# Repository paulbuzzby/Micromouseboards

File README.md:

# Micromouseboards
Here are different sets of PCBs for various Micro Mouse applications. This is the start of me using KiCad. I make no promises that any of this works.

Some of these boards (MouseSMDUKMARSAdvancedBoard and MouseMainboardTemplate) started as UKMARS boards that can be found [Here](https://github.com/ukmars/ukmarsbot)

All credit to Peter Harrison for the original design of these boards

Circuit design for the other boards is credited to Duncan Louttit

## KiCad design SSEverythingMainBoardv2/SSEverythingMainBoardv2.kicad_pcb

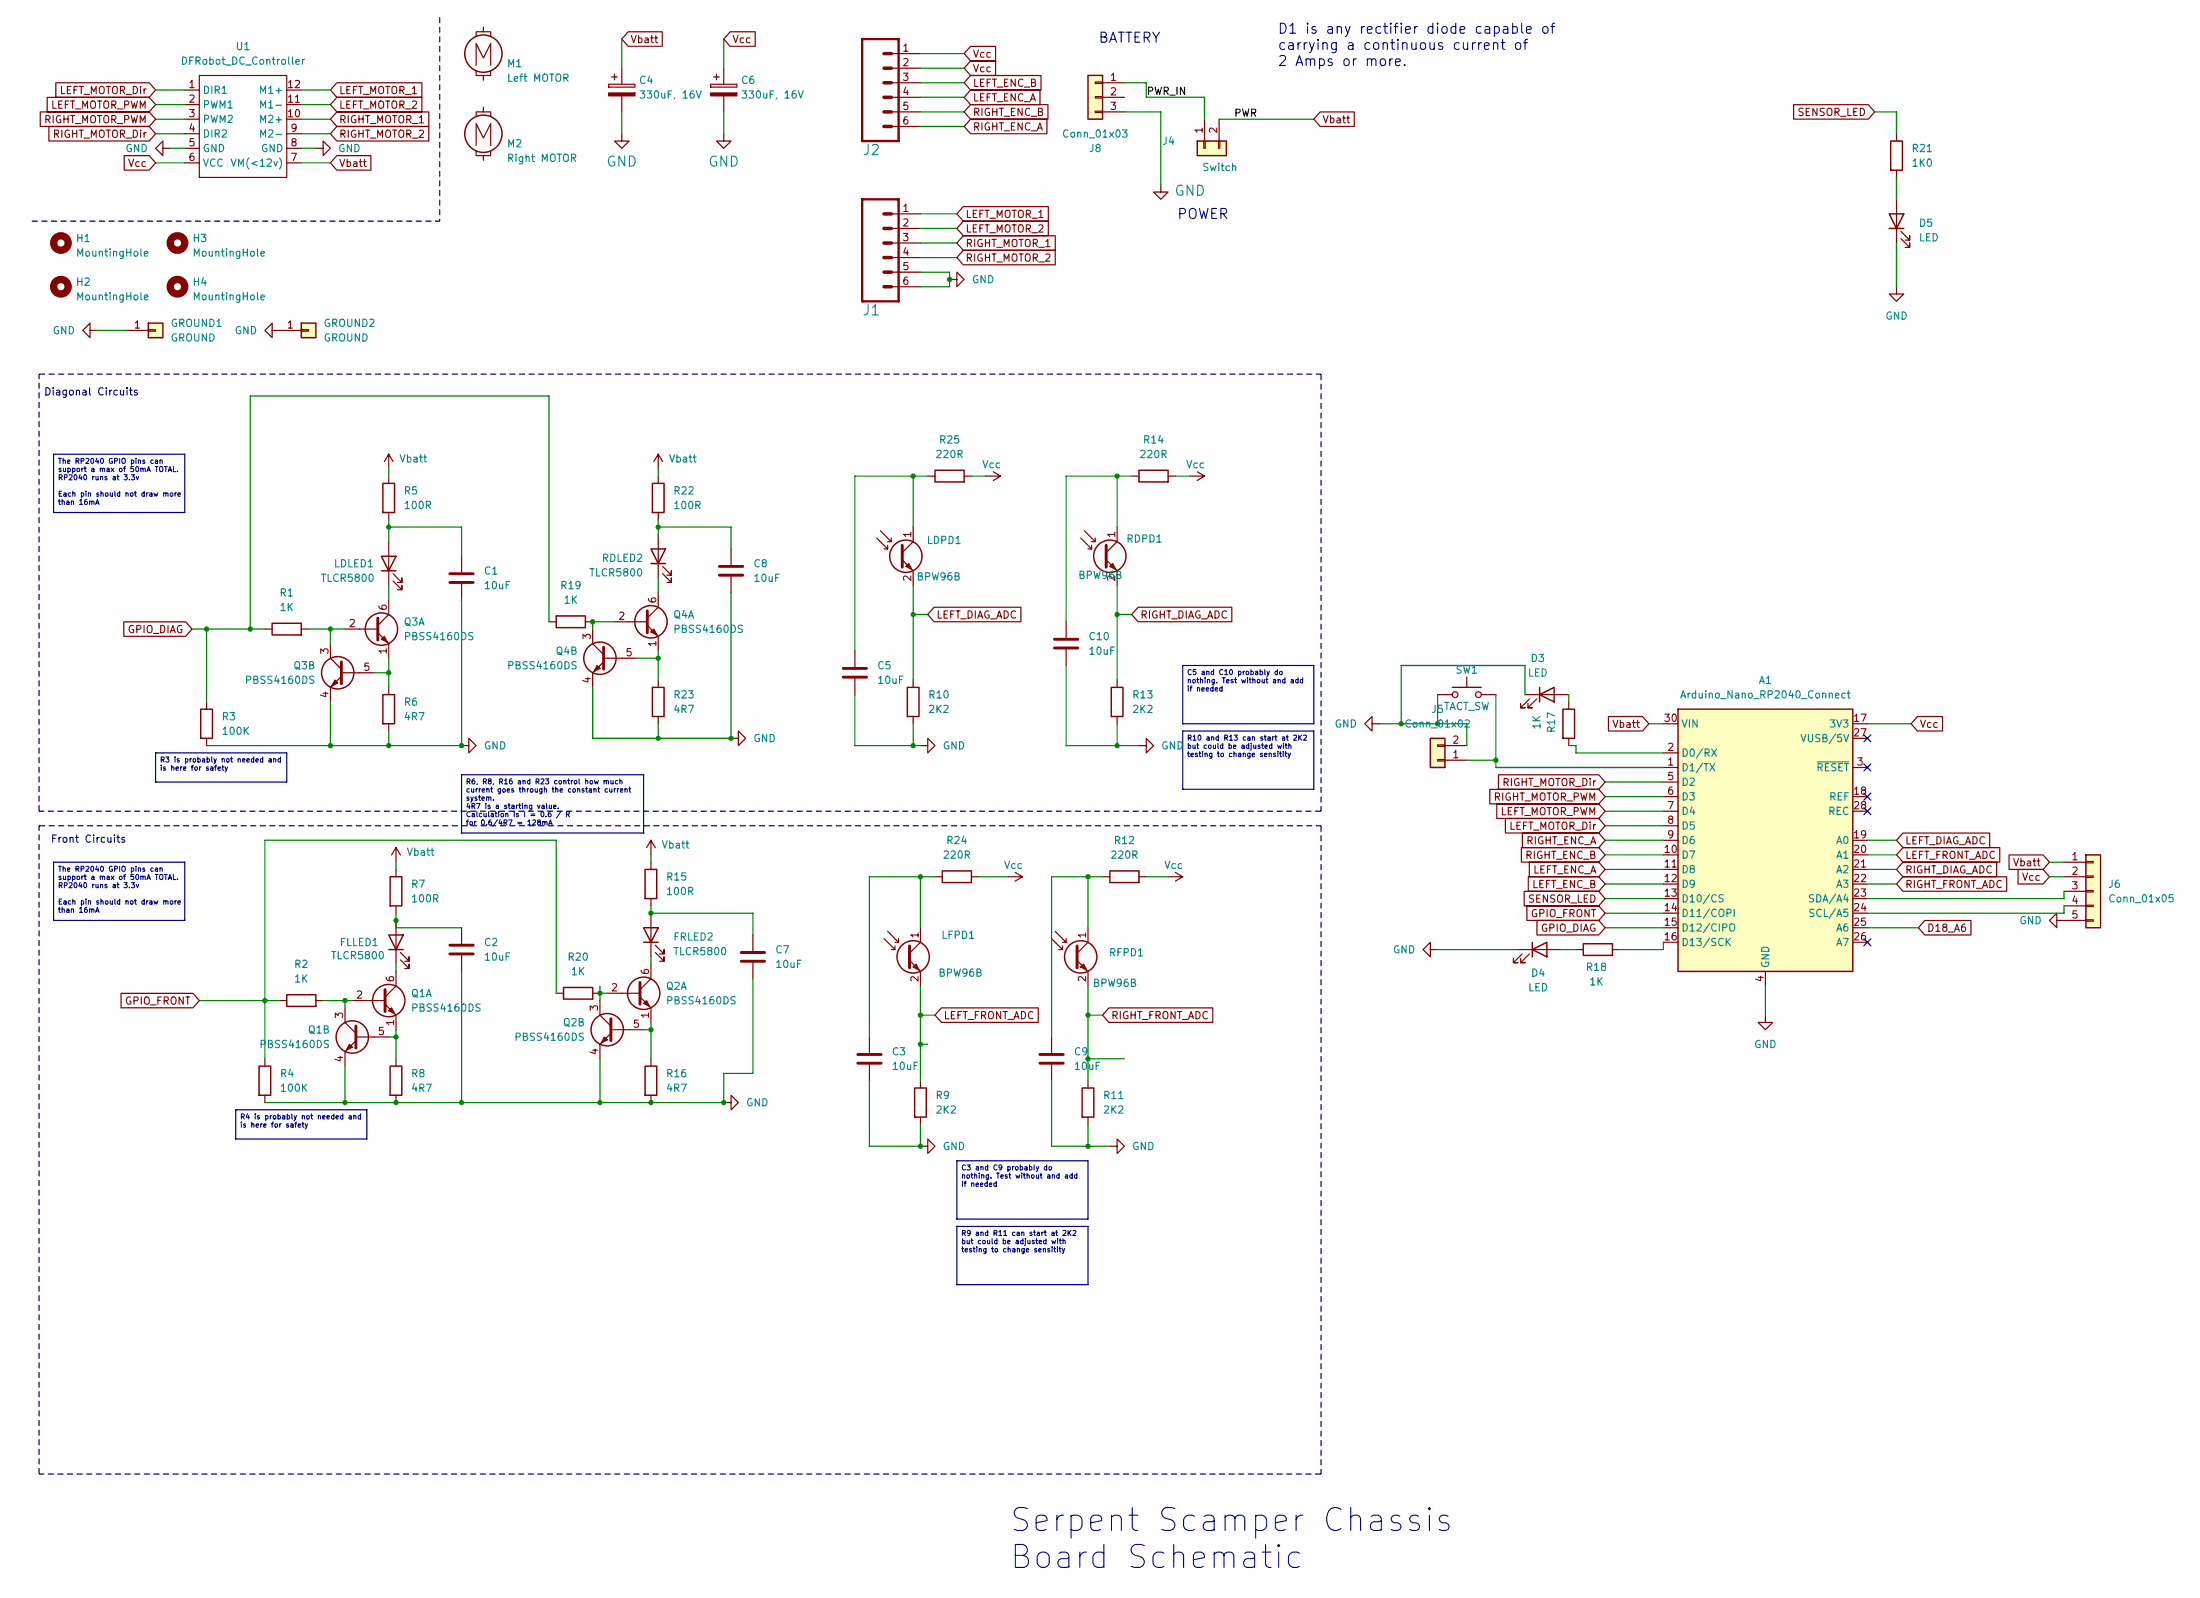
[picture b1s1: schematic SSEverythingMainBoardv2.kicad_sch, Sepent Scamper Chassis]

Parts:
A1: Arduino_Nano_RP2040_Connect; Arduino_Nano
C1, C2, C3, C5, C7, C8, C9, C10: 10uF; C_1206_3216Metric_Pad1.33x1.80mm_HandSolder
C4, C6: 330uF, 16V; C_Radial_D6.3mm_H7.0mm_P2.50mm
D3, D4, D5: LED; LED_1206_3216Metric_Pad1.42x1.75mm_HandSolder
FLLED1: TLCR5800; LED_D5.0mm_Horizontal_O1.27mm_Z3.0mm
FRLED2: TLCR5800; LED_D5.0mm_Horizontal_O1.27mm_Z3.0mm
GROUND1, GROUND2: GROUND; PinHeader_1x01_P2.54mm_Vertical
H1, H2, H3, H4: MountingHole; MountingHole_3.2mm_M3_clearance
J1, J2: CONN_06SILK_FEMALE_PTH; 1X06_LOCK_LONGPADS
J4: Switch; PinHeader_1x02_P2.54mm_Vertical
J5: Conn_01x02; PinHeader_1x02_P2.54mm_Vertical
J6: Conn_01x05; PinSocket_1x05_P2.54mm_Vertical
J8: Conn_01x03; JST_XH_B3B-XH-A_1x03_P2.50mm_Vertical
LDLED1: TLCR5800; LED_D5.0mm_Horizontal_O1.27mm_Z3.0mm
LDPD1: BPW96B; LED_D5.0mm_Horizontal_O1.27mm_Z3.0mm
LFPD1: BPW96B; LED_D5.0mm_Horizontal_O1.27mm_Z3.0mm
M1: Left MOTOR; MINI-METAL-GEARMOTOR-WITH-BRACKET
M2: Right MOTOR; MINI-METAL-GEARMOTOR-WITH-BRACKET_Alt
Q1, Q2, Q3, Q4: PBSS4160DS; SOT95P275X110-6N
R1, R2, R17, R18, R19, R20: 1K; R_0805_2012Metric_Pad1.20x1.40mm_HandSolder
R3, R4: 100K; R_0805_2012Metric_Pad1.20x1.40mm_HandSolder
R5, R7, R15, R22: 100R; R_0805_2012Metric_Pad1.20x1.40mm_HandSolder
R6, R8, R16, R23: 4R7; R_0805_2012Metric_Pad1.20x1.40mm_HandSolder
R9, R10, R11, R13: 2K2; R_0805_2012Metric_Pad1.20x1.40mm_HandSolder
R12, R14, R24, R25: 220R; R_0805_2012Metric_Pad1.20x1.40mm_HandSolder
R21: 1K0; R_0805_2012Metric_Pad1.20x1.40mm_HandSolder
RDLED2: TLCR5800; LED_D5.0mm_Horizontal_O1.27mm_Z3.0mm
RDPD1: BPW96B; LED_D5.0mm_Horizontal_O1.27mm_Z3.0mm
RFPD1: BPW96B; LED_D5.0mm_Horizontal_O1.27mm_Z3.0mm
SW1: TACT_SW; SW_PUSH_6mm
U1: DFRobot_DC_Controller

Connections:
/PWR_IN: J4.1, J8.1
D18_A6: A1.25 (A6)
GND: A1.4 (GND), A1.29 (GND), C1.1, C2.1, C3.2, C4.2, C5.2, C6.2, C7.1, C8.1, C9.2, C10.2, D3.1 (K), D4.1 (K), D5.1 (K), GROUND1.1, GROUND2.1, J1.5, J1.6, J5.2, J6.5, J8.3, Q1.4 (E2), Q2.4 (E2), Q3.4 (E2), Q4.4 (E2), R3.2, R4.2, R6.2, R8.2, R9.2, R10.2, R11.2, R13.2, R16.2, R23.2, SW1.1 (A), U1.5 (GND), U1.8 (GND)
GPIO_DIAG: A1.15 (D12/CIPO), R1.1, R3.1, R19.2
GPIO_FRONT: A1.14 (D11/COPI), R2.1, R4.1, R20.1
LEFT_DIAG_ADC: A1.19 (A0), LDPD1.2 (E), R10.1
LEFT_ENC_A: A1.11 (D8), J2.4
LEFT_ENC_B: A1.12 (D9), J2.3
LEFT_FRONT_ADC: A1.20 (A1), LFPD1.2 (E), R9.1
LEFT_MOTOR_1: J1.1, U1.12 (M1+)
LEFT_MOTOR_2: J1.2, U1.11 (M1-)
LEFT_MOTOR_Dir: A1.8 (D5), U1.1 (DIR1)
LEFT_MOTOR_PWM: A1.7 (D4), U1.2 (PWM1)
unnamed: A1.2 (D0/RX), R17.2
unnamed: A1.1 (D1/TX), J5.1, SW1.2 (B)
unnamed: A1.16 (D13/SCK), R18.2
unnamed: A1.24 (SCL/A5), J6.4
unnamed: A1.23 (SDA/A4), J6.3
unnamed: D3.2 (A), R17.1
unnamed: D4.2 (A), R18.1
unnamed: D5.2 (A), R21.2
unnamed: C2.2, FLLED1.2 (A), R7.2
unnamed: FLLED1.1 (K), Q1.6 (C1)
unnamed: C7.2, FRLED2.2 (A), R15.2
unnamed: FRLED2.1 (K), Q2.6 (C1)
unnamed: C1.2, LDLED1.2 (A), R5.2
unnamed: LDLED1.1 (K), Q3.6 (C1)
unnamed: C5.1, LDPD1.1 (C), R25.1
unnamed: C3.1, LFPD1.1 (C), R24.1
unnamed: Q1.2 (B1), Q1.3 (C2), R2.2
unnamed: Q1.1 (E1), Q1.5 (B2), R8.1
unnamed: Q2.2 (B1), Q2.3 (C2), R20.2
unnamed: Q2.1 (E1), Q2.5 (B2), R16.1
unnamed: Q3.2 (B1), Q3.3 (C2), R1.2
unnamed: Q3.1 (E1), Q3.5 (B2), R6.1
unnamed: Q4.2 (B1), Q4.3 (C2), R19.1
unnamed: Q4.6 (C1), RDLED2.1 (K)
unnamed: Q4.1 (E1), Q4.5 (B2), R23.1
unnamed: C8.2, R22.2, RDLED2.2 (A)
unnamed: C10.1, R14.1, RDPD1.1 (C)
unnamed: C9.1, R12.1, RFPD1.1 (C)
RIGHT_DIAG_ADC: A1.21 (A2), R13.1, RDPD1.2 (E)
RIGHT_ENC_A: A1.9 (D6), J2.6
RIGHT_ENC_B: A1.10 (D7), J2.5
RIGHT_FRONT_ADC: A1.22 (A3), R11.1, RFPD1.2 (E)
RIGHT_MOTOR_1: J1.3, U1.10 (M2+)
RIGHT_MOTOR_2: J1.4, U1.9 (M2-)
RIGHT_MOTOR_Dir: A1.5 (D2), U1.4 (DIR2)
RIGHT_MOTOR_PWM: A1.6 (D3), U1.3 (PWM2)
SENSOR_LED: A1.13 (D10/CS), R21.1
Vbatt: A1.30 (VIN), C4.1, J4.2, J6.1, R5.1, R7.1, R15.1, R22.1, U1.7 (VM(<12v))
Vcc: A1.17 (3V3), C6.1, J2.1, J2.2, J6.2, R12.2, R14.2, R24.2, R25.2, U1.6 (VCC)

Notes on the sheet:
D1 is any rectifier diode capable of carrying a continuous current of 2 Amps or more.
Front Circuits
POWER
Diagonal Circuits
BATTERY
Serpent Scamper Chassis Board Schematic
R10 and R13 can start at 2K2 but could be adjusted with testing to change sensitity
C3 and C9 probably do nothing. Test without and add if needed
R3 is probably not needed and is here for safety
R6, R8, R16 and R23 control how much current goes through the constant current system. 4R7 is a starting value. Calculation is I = 0.6 / R for 0.6/4R7 = 128mA
C5 and C10 probably do nothing. Test without and add if needed
The RP2040 GPIO pins can support a max of 50mA TOTAL. RP2040 runs at 3.3v Each pin should not draw more than 16mA
R4 is probably not needed and is here for safety
R9 and R11 can start at 2K2 but could be adjusted with testing to change sensitity

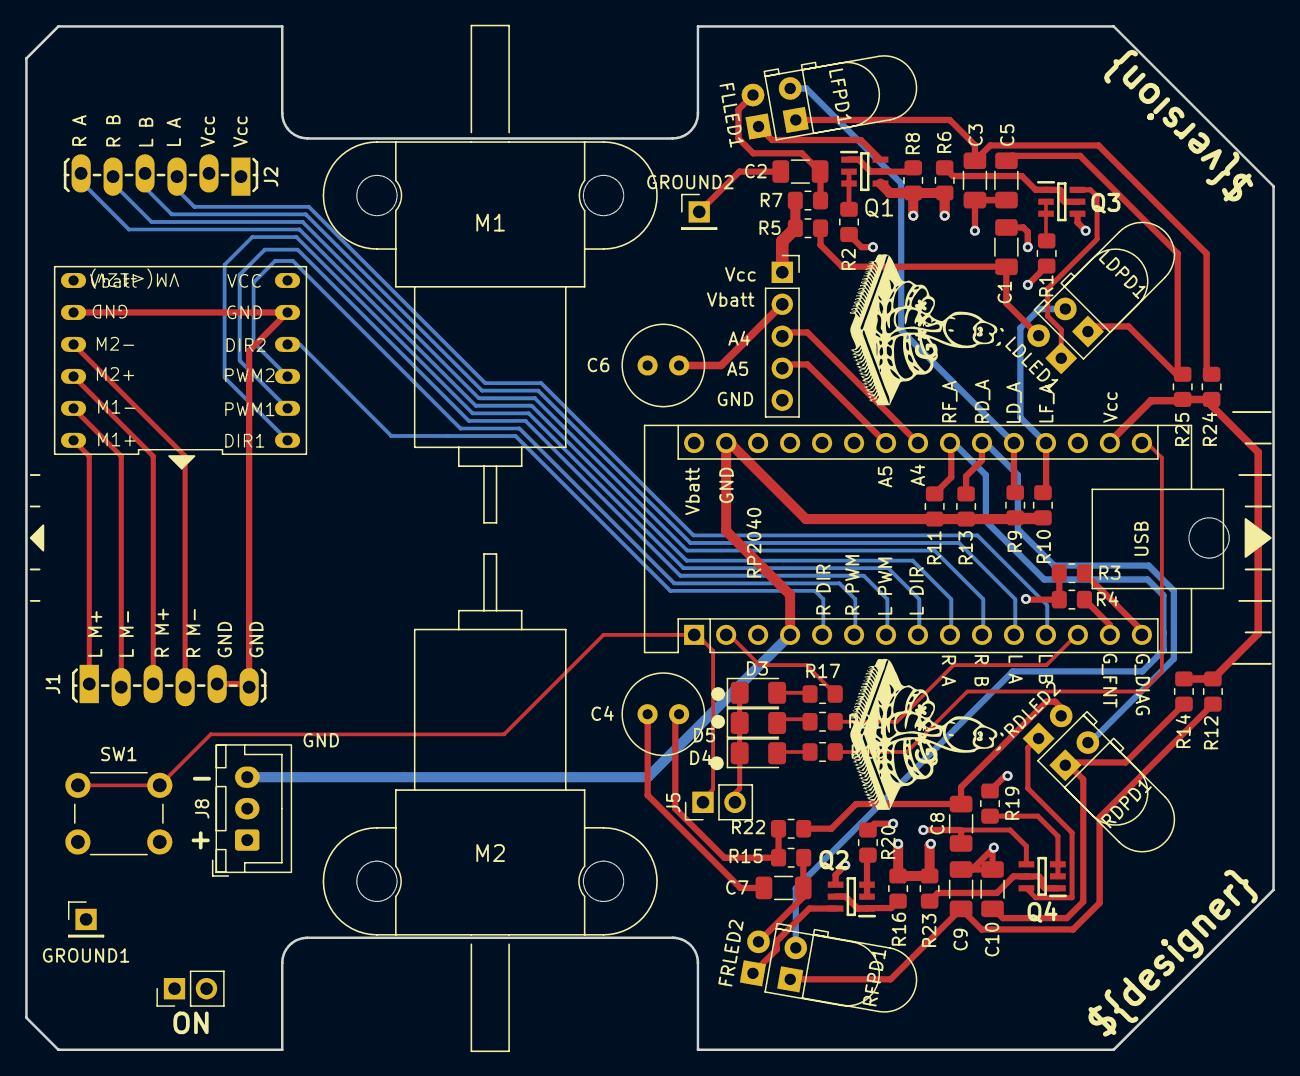
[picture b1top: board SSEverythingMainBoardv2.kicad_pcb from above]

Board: 4 copper layers, 99.1 x 81.3 mm, 67 parts (0 on the bottom side), 51 nets.

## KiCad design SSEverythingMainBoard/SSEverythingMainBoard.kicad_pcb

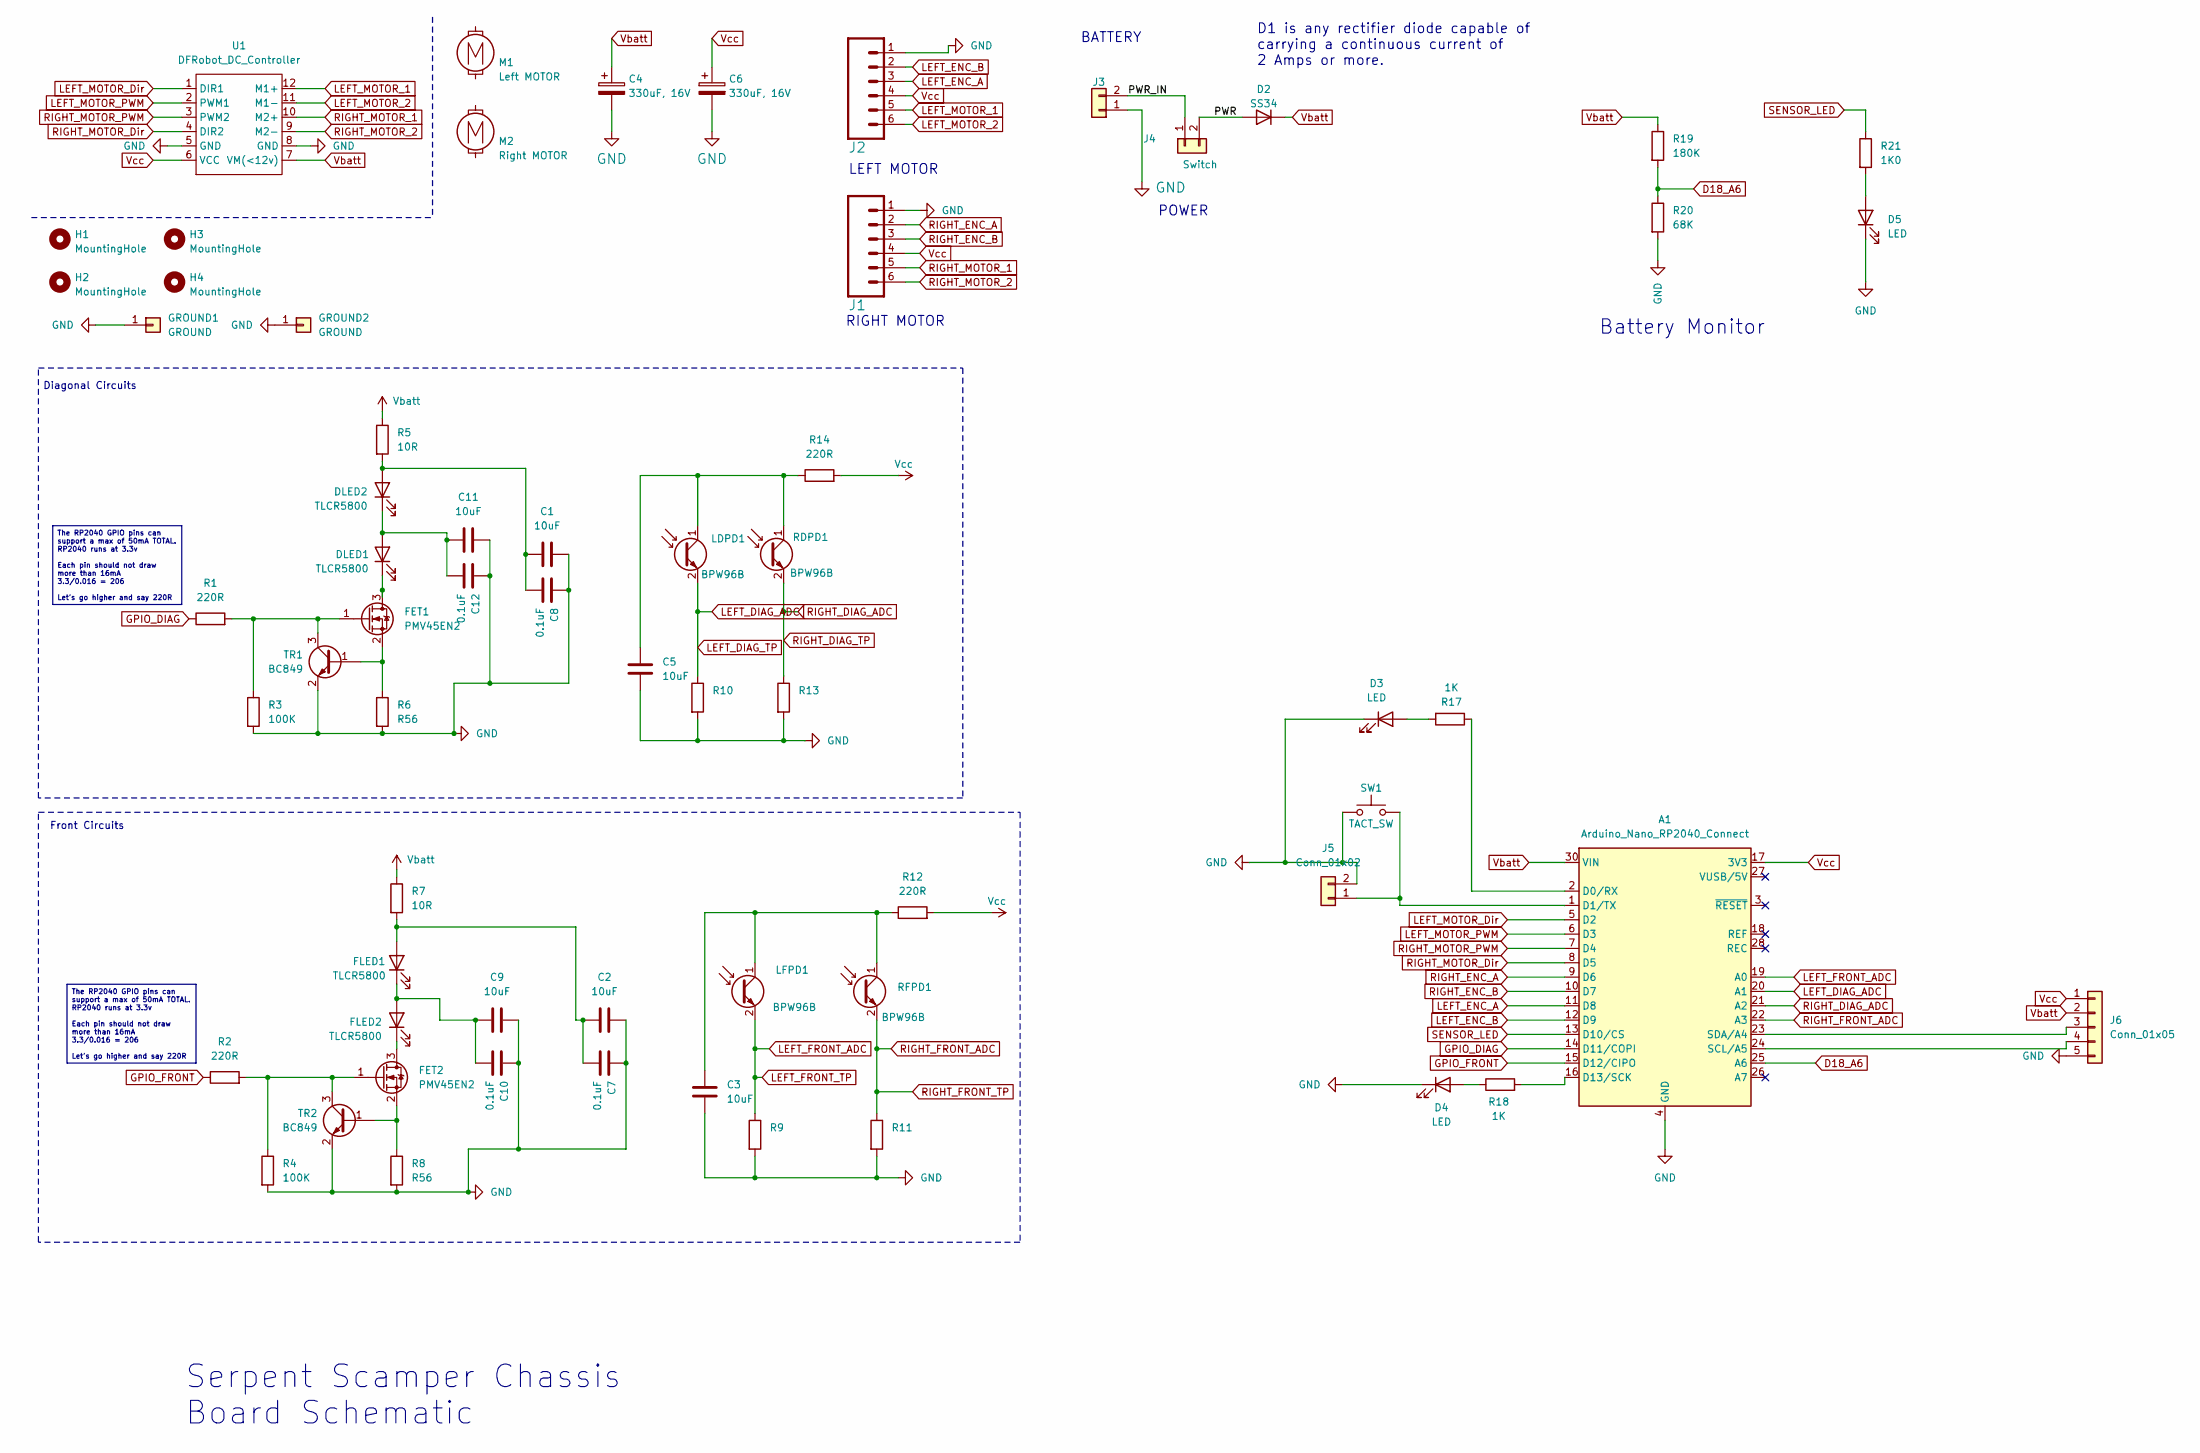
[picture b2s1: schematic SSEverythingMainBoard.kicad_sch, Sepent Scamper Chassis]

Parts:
A1: Arduino_Nano_RP2040_Connect; Arduino_Nano
C1, C2, C3, C5, C9, C11: 10uF; C_0805_2012Metric_Pad1.18x1.45mm_HandSolder
C4, C6: 330uF, 16V; CP_Radial_D8.0mm_P2.50mm
C7, C8, C10, C12: 0.1uF; C_0805_2012Metric_Pad1.18x1.45mm_HandSolder
D2: SS34; D_SMC
D3, D4, D5: LED; LED_1206_3216Metric_Pad1.42x1.75mm_HandSolder
DLED1, DLED2: TLCR5800; LED_D5.0mm_Horizontal_O1.27mm_Z3.0mm
FET1, FET2: PMV45EN2; SOT-23_Handsoldering
FLED1, FLED2: TLCR5800; LED_D5.0mm_Horizontal_O1.27mm_Z3.0mm
GROUND1, GROUND2: GROUND; PinHeader_1x01_P2.54mm_Vertical
H1, H2, H3, H4: MountingHole; MountingHole_3.2mm_M3_clearance
J1, J2: CONN_06SILK_FEMALE_PTH; 1X06_LOCK_LONGPADS
J3: POWER; PinHeader_1x02_P2.54mm_Vertical
J4: Switch; PinHeader_1x02_P2.54mm_Vertical
J5: Conn_01x02; PinHeader_1x02_P2.54mm_Vertical
J6: Conn_01x05; PinSocket_1x05_P2.54mm_Vertical
LDPD1: BPW96B; LED_D5.0mm_Horizontal_O1.27mm_Z3.0mm
LFPD1: BPW96B; LED_D5.0mm_Horizontal_O1.27mm_Z3.0mm
M1: Left MOTOR; MINI-METAL-GEARMOTOR-WITH-BRACKET_Alt
M2: Right MOTOR; MINI-METAL-GEARMOTOR-WITH-BRACKET
R1, R2, R12, R14: 220R; R_0805_2012Metric_Pad1.20x1.40mm_HandSolder
R3, R4: 100K; R_0805_2012Metric_Pad1.20x1.40mm_HandSolder
R5, R7: 10R; R_0805_2012Metric_Pad1.20x1.40mm_HandSolder
R6, R8: R56; R_0805_2012Metric_Pad1.20x1.40mm_HandSolder
R9, R10, R11, R13: R; R_0805_2012Metric_Pad1.20x1.40mm_HandSolder
R17, R18: 1K; R_0805_2012Metric_Pad1.20x1.40mm_HandSolder
R19: 180K; R_0805_2012Metric_Pad1.20x1.40mm_HandSolder
R20: 68K; R_0805_2012Metric_Pad1.20x1.40mm_HandSolder
R21: 1K0; R_0805_2012Metric_Pad1.20x1.40mm_HandSolder
RDPD1: BPW96B; LED_D5.0mm_Horizontal_O1.27mm_Z3.0mm
RFPD1: BPW96B; LED_D5.0mm_Horizontal_O1.27mm_Z3.0mm
SW1: TACT_SW; SW_PUSH_6mm
TR1, TR2: BC849; SOT-23_Handsoldering
U1: DFRobot_DC_Controller

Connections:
/PWR: D2.2 (A), J4.2
/PWR_IN: J3.2, J4.1
D18_A6: A1.25 (A6), R19.2, R20.1
GND: A1.4 (GND), A1.29 (GND), C1.2, C2.2, C3.2, C4.2, C5.2, C6.2, C7.1, C8.1, C9.2, C10.1, C11.2, C12.1, D3.1 (K), D4.1 (K), D5.1 (K), GROUND1.1, GROUND2.1, J1.1, J2.1, J3.1, J5.2, J6.5, R3.2, R4.2, R6.2, R8.2, R9.2, R10.2, R11.2, R13.2, R20.2, SW1.1 (A), TR1.2 (E), TR2.2 (E), U1.5 (GND), U1.8 (GND)
GPIO_DIAG: A1.14 (D11/COPI), R1.1
GPIO_FRONT: A1.15 (D12/CIPO), R2.1
LEFT_DIAG_ADC: A1.20 (A1), LDPD1.2 (E), R10.1
LEFT_ENC_A: A1.11 (D8), J2.3
LEFT_ENC_B: A1.12 (D9), J2.2
LEFT_FRONT_ADC: A1.19 (A0), LFPD1.2 (E), R9.1
LEFT_MOTOR_1: J2.5, U1.12 (M1+)
LEFT_MOTOR_2: J2.6, U1.11 (M1-)
LEFT_MOTOR_Dir: A1.5 (D2), U1.1 (DIR1)
LEFT_MOTOR_PWM: A1.6 (D3), U1.2 (PWM1)
unnamed: A1.2 (D0/RX), R17.1
unnamed: A1.1 (D1/TX), J5.1, SW1.2 (B)
unnamed: A1.16 (D13/SCK), R18.2
unnamed: A1.24 (SCL/A5), J6.4
unnamed: A1.23 (SDA/A4), J6.3
unnamed: D3.2 (A), R17.2
unnamed: D4.2 (A), R18.1
unnamed: D5.2 (A), R21.2
unnamed: C11.1, C12.2, DLED1.2 (A), DLED2.1 (K)
unnamed: DLED1.1 (K), FET1.3 (D)
unnamed: C1.1, C8.2, DLED2.2 (A), R5.2
unnamed: FET1.1 (G), R1.2, R3.1, TR1.3 (C)
unnamed: FET1.2 (S), R6.1, TR1.1 (B)
unnamed: FET2.3 (D), FLED2.1 (K)
unnamed: FET2.1 (G), R2.2, R4.1, TR2.3 (C)
unnamed: FET2.2 (S), R8.1, TR2.1 (B)
unnamed: C2.1, C7.2, FLED1.2 (A), R7.2
unnamed: C9.1, C10.2, FLED1.1 (K), FLED2.2 (A)
unnamed: C5.1, LDPD1.1 (C), R14.1, RDPD1.1 (C)
unnamed: C3.1, LFPD1.1 (C), R12.1, RFPD1.1 (C)
RIGHT_DIAG_ADC: A1.21 (A2), R13.1, RDPD1.2 (E)
RIGHT_ENC_A: A1.9 (D6), J1.2
RIGHT_ENC_B: A1.10 (D7), J1.3
RIGHT_FRONT_ADC: A1.22 (A3), R11.1, RFPD1.2 (E)
RIGHT_MOTOR_1: J1.5, U1.10 (M2+)
RIGHT_MOTOR_2: J1.6, U1.9 (M2-)
RIGHT_MOTOR_Dir: A1.8 (D5), U1.4 (DIR2)
RIGHT_MOTOR_PWM: A1.7 (D4), U1.3 (PWM2)
SENSOR_LED: A1.13 (D10/CS), R21.1
Vbatt: A1.30 (VIN), C4.1, D2.1 (K), J6.2, R5.1, R7.1, R19.1, U1.7 (VM(<12v))
Vcc: A1.17 (3V3), C6.1, J1.4, J2.4, J6.1, R12.2, R14.2, U1.6 (VCC)

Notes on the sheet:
The RP2040 GPIO pins can support a max of 50mA TOTAL. RP2040 runs at 3.3v Each pin should not draw more than 16mA 3.3/0.016 = 206 Let's go higher and say 220R
D1 is any rectifier diode capable of carrying a continuous current of 2 Amps or more.
Front Circuits
POWER
Diagonal Circuits
RIGHT MOTOR
BATTERY
Serpent Scamper Chassis Board Schematic
LEFT MOTOR
Battery Monitor

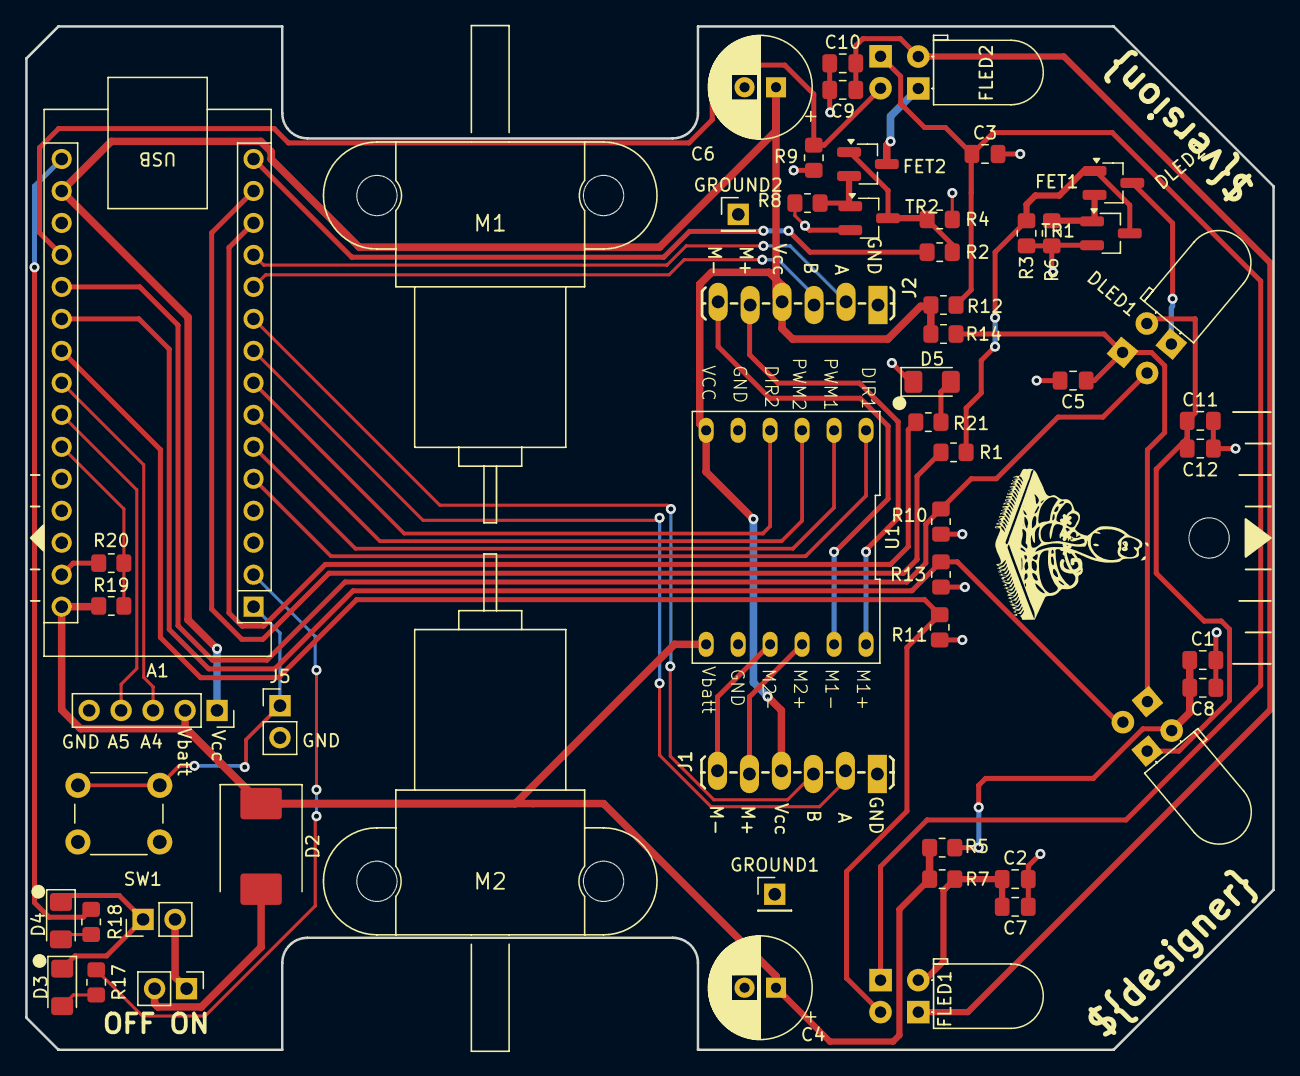
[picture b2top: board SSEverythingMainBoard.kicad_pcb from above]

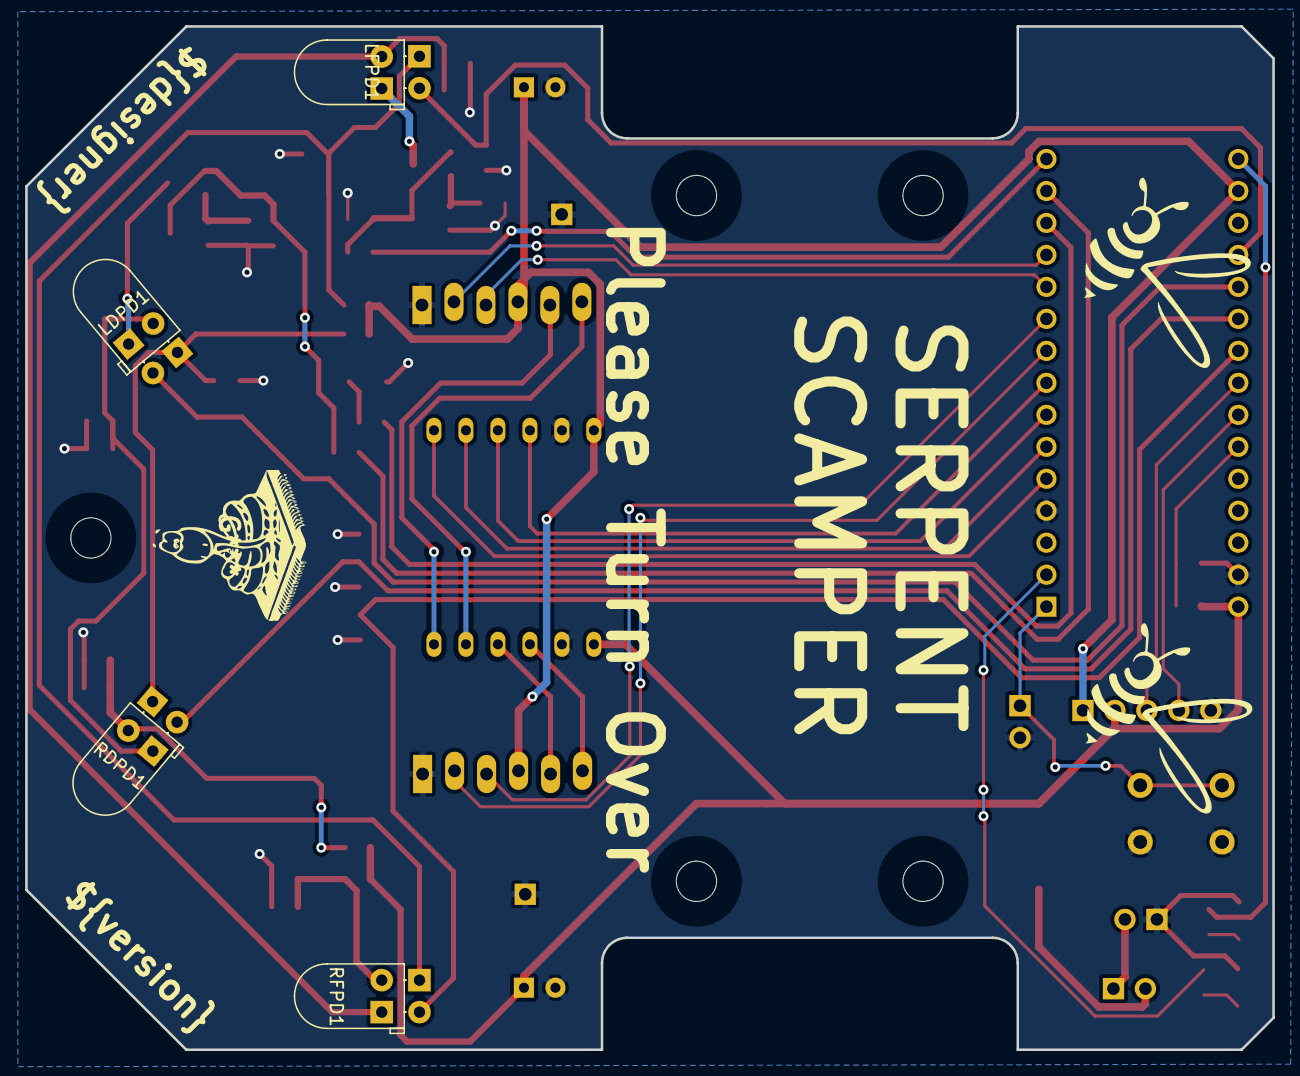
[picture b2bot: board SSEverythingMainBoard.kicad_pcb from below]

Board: 2 copper layers, 99.1 x 81.3 mm, 64 parts (4 on the bottom side), 45 nets.

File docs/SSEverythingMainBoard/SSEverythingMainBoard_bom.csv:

Reference,Value,Qty,Note,Description
A1,Arduino_Nano_RP2040_Connect,1,,"Arduino Nano board based on the RP2040 microcontroller with a dual-core 133 MHz ARM Cortex-M0+ processor, 264 kB SRAM, and up to 16 MB flash memory. Operates at 3.3V, with 5V Micro USB input and 4-20V VIN. Features Wi-Fi®, Bluetooth® LE, digital and analog pins, and supports SPI, I2C, UART, and PIO. Includes a 6-axis IMU, RGB LED, microphone, and cryptographic chip for secure communication."
C7 C8 C10 C12,0.1uF,4,,
C1 C2 C3 C5 C9 C11,10uF,6,,Unpolarized capacitor
C4 C6,"330uF, 16V",2,Maximum height is 10mm,
D3 D4 D5,LED,3,,Light emitting diode
D2,SS34,1,RS - 808-0433,"onsemi 40V 3A, Schottky Diode"
DLED1 DLED2 FLED1 FLED2,TLCR5800,4,,Light emitting diode
FET1 FET2,PMV45EN2,2,,"N-Channel MOSFET, 5.1 A, 30 V, 3-Pin SOT-23"
GROUND1 GROUND2 J3 J4 J5 J6,GROUND,6,"0.1"" pitch, polarised, any type","Generic connector, single row, 01x01, script generated (kicad-library-utils/schlib/autogen/connector/) Generic connector, single row, 01x02, script generated (kicad-library-utils/schlib/autogen/connector/) Generic connector, single row, 01x05, script generated (kicad-library-utils/schlib/autogen/connector/)"
J1 J2,CONN_06SILK_FEMALE_PTH,2,"6 pin header, 0.1"", male",
LDPD1 LFPD1 RDPD1 RFPD1,BPW96B,4,,Photodiode
M1,Left MOTOR,1,commercial mounts need bushing for screws,
M2,Right MOTOR,1,commercial mounts need bushing for screws,
R3 R4,100K,2,,Resistor
R5 R7,10R,2,,Resistor
R19,180K,1,,Resistor
R17 R18,1K,2,,Resistor
R21,1K0,1,,Resistor
R1 R2 R12 R14,220R,4,,Resistor
R20,68K,1,,Resistor
R9 R10 R11 R13,R,4,,Resistor
R6 R8,R56,2,,Resistor
SW1,TACT_SW,1,,TACT switch 6mm 4.5mm
TR1 TR2,BC849,2,,"0.1A Ic, 30V Vce, NPN Transistor, SOT-23"
U1,DFRobot_DC_Controller,1,,
